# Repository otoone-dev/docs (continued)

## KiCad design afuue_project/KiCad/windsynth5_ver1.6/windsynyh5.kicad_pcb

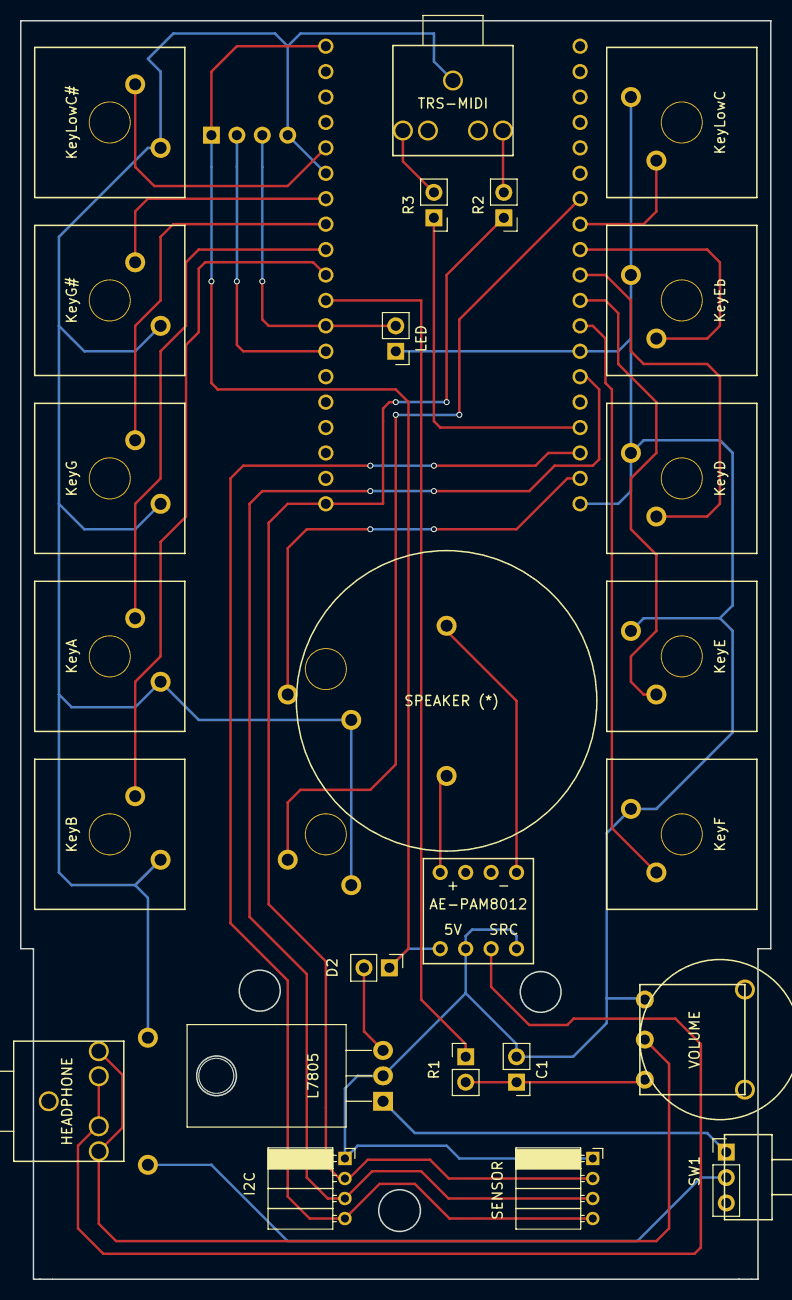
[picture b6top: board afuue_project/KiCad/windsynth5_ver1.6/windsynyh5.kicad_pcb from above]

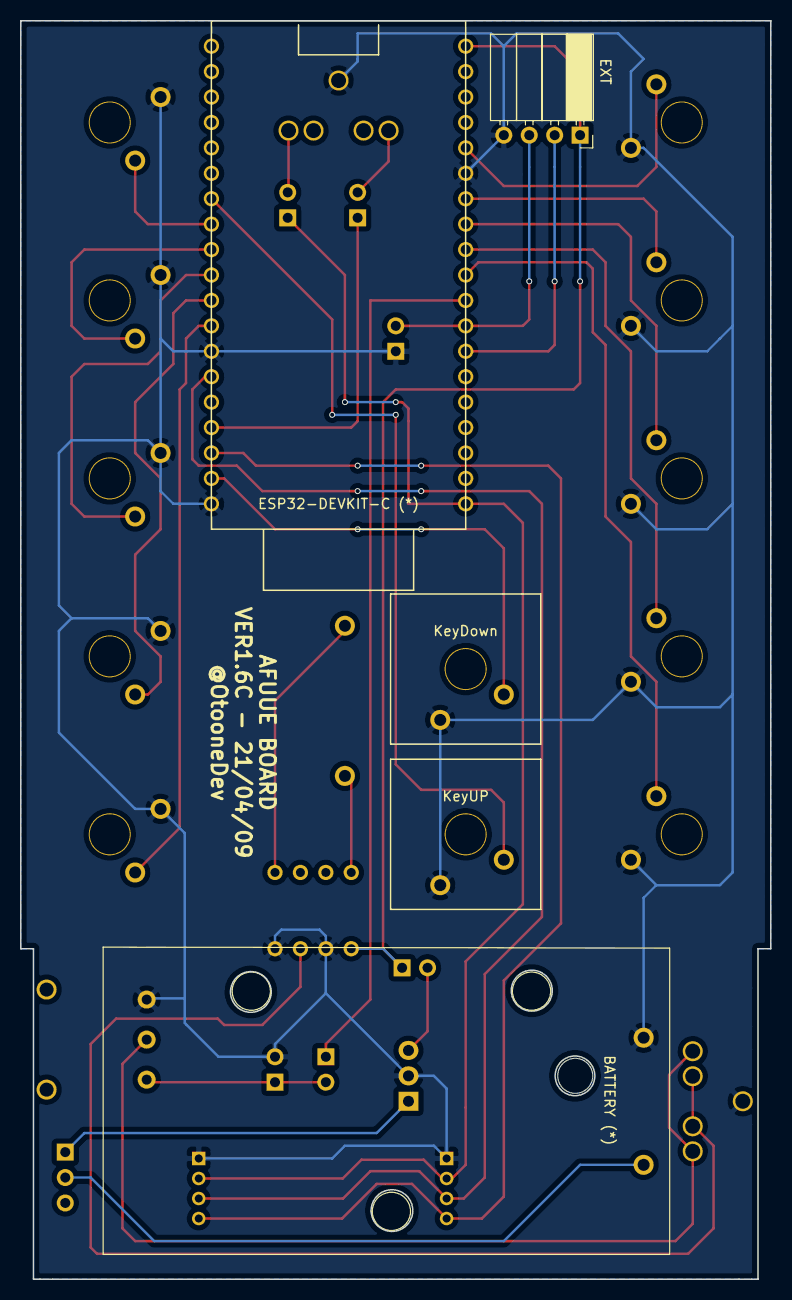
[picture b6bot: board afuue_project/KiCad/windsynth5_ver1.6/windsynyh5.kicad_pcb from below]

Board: 2 copper layers, 74.9 x 125.7 mm, 30 parts (5 on the bottom side), 31 nets.

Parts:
AE-PAM8012: AE-PAM8012
BATTERY (*): POWER; BH-9V-3P24
C1: C; Pin_Header_Straight_1x02_Pitch2.54mm
D2: 1N5822; PinHeader_1x02_P2.54mm_Vertical
ESP32-DEVKIT-C (*): ESP32-DEVKIT-C
EXT: EXT; Socket_Strip_Angled_1x04_Pitch2.54mm
HEADPHONE: HEADPHONE; PJ-307 AudioJack
I2C: I2C; Socket_Strip_Angled_1x04_Pitch2.00mm
KeyA: KeyA; CherryMX-Switch
KeyB: KeyB; CherryMX-Switch
KeyD: KeyD; CherryMX-Switch
KeyDown: KeyDown; CherryMX-Switch
KeyE: KeyE; CherryMX-Switch
KeyEb: KeyEb; CherryMX-Switch
KeyF: KeyF; CherryMX-Switch
KeyG: KeyG; CherryMX-Switch
KeyG#: KeyG#; CherryMX-Switch
KeyLowC: KeyLowC; CherryMX-Switch
KeyLowC#: KeyLowC#; CherryMX-Switch
KeyUP: KeyUp; CherryMX-Switch
L7805: L7805; TO-220-3_Horizontal_TabDown
LED: Led_Small; Pin_Header_Straight_1x02_Pitch2.54mm
R1: 510; Pin_Header_Straight_1x02_Pitch2.54mm
R2, R3: 47; Pin_Header_Straight_1x02_Pitch2.54mm
SENSOR: SENSOR; Socket_Strip_Angled_1x04_Pitch2.00mm
SPEAKER (*): SPEAKER; USGM30
SW1: SW_SPDT; PinHeader_1x03_P2.54mm_Vertical
TRS-MIDI: TRS MIDI; PJ-307 AudioJack
VOLUME: POT; R1001-N16

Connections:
+5V: AE-PAM8012.1, D2.1, ESP32-DEVKIT-C (*).19, EXT.1
+9V: L7805.1, SW1.1
GND: AE-PAM8012.2, AE-PAM8012.4, BATTERY (*).2, C1.2, ESP32-DEVKIT-C (*).14, ESP32-DEVKIT-C (*).32, ESP32-DEVKIT-C (*).38, EXT.4, HEADPHONE.1, I2C.1, KeyA.2, KeyB.2, KeyD.2, KeyDown.2, KeyE.2, KeyEb.2, KeyF.2, KeyG.2, KeyG#.2, KeyLowC.2, KeyLowC#.2, KeyUP.2, L7805.2, LED.1, SENSOR.1, TRS-MIDI.1, VOLUME.1
unnamed: C1.1, R1.2, VOLUME.3
unnamed: ESP32-DEVKIT-C (*).8, EXT.3, LED.2
unnamed: D2.2, L7805.3
unnamed: ESP32-DEVKIT-C (*).11, KeyA.1
unnamed: ESP32-DEVKIT-C (*).10, KeyB.1
unnamed: ESP32-DEVKIT-C (*).29, KeyD.1
unnamed: ESP32-DEVKIT-C (*).37, KeyDown.1
unnamed: ESP32-DEVKIT-C (*).30, KeyE.1
unnamed: ESP32-DEVKIT-C (*).28, KeyEb.1
unnamed: ESP32-DEVKIT-C (*).31, KeyF.1
unnamed: ESP32-DEVKIT-C (*).12, KeyG.1
unnamed: ESP32-DEVKIT-C (*).13, KeyG#.1
unnamed: ESP32-DEVKIT-C (*).27, KeyLowC.1
unnamed: ESP32-DEVKIT-C (*).15, KeyLowC#.1
unnamed: ESP32-DEVKIT-C (*).26, KeyUP.1
unnamed: ESP32-DEVKIT-C (*).1, I2C.2, R2.1, SENSOR.2
unnamed: ESP32-DEVKIT-C (*).33, I2C.3, SENSOR.3
unnamed: ESP32-DEVKIT-C (*).36, I2C.4, SENSOR.4
unnamed: AE-PAM8012.5, SPEAKER (*).1
unnamed: AE-PAM8012.8, SPEAKER (*).2
unnamed: HEADPHONE.2, HEADPHONE.5, VOLUME.2
unnamed: AE-PAM8012.3, HEADPHONE.3, HEADPHONE.4
unnamed: BATTERY (*).1, SW1.2
unnamed: ESP32-DEVKIT-C (*).7, EXT.2
unnamed: R3.2, TRS-MIDI.2
unnamed: R2.2, TRS-MIDI.5
unnamed: ESP32-DEVKIT-C (*).9, R1.1
unnamed: ESP32-DEVKIT-C (*).35, R3.1

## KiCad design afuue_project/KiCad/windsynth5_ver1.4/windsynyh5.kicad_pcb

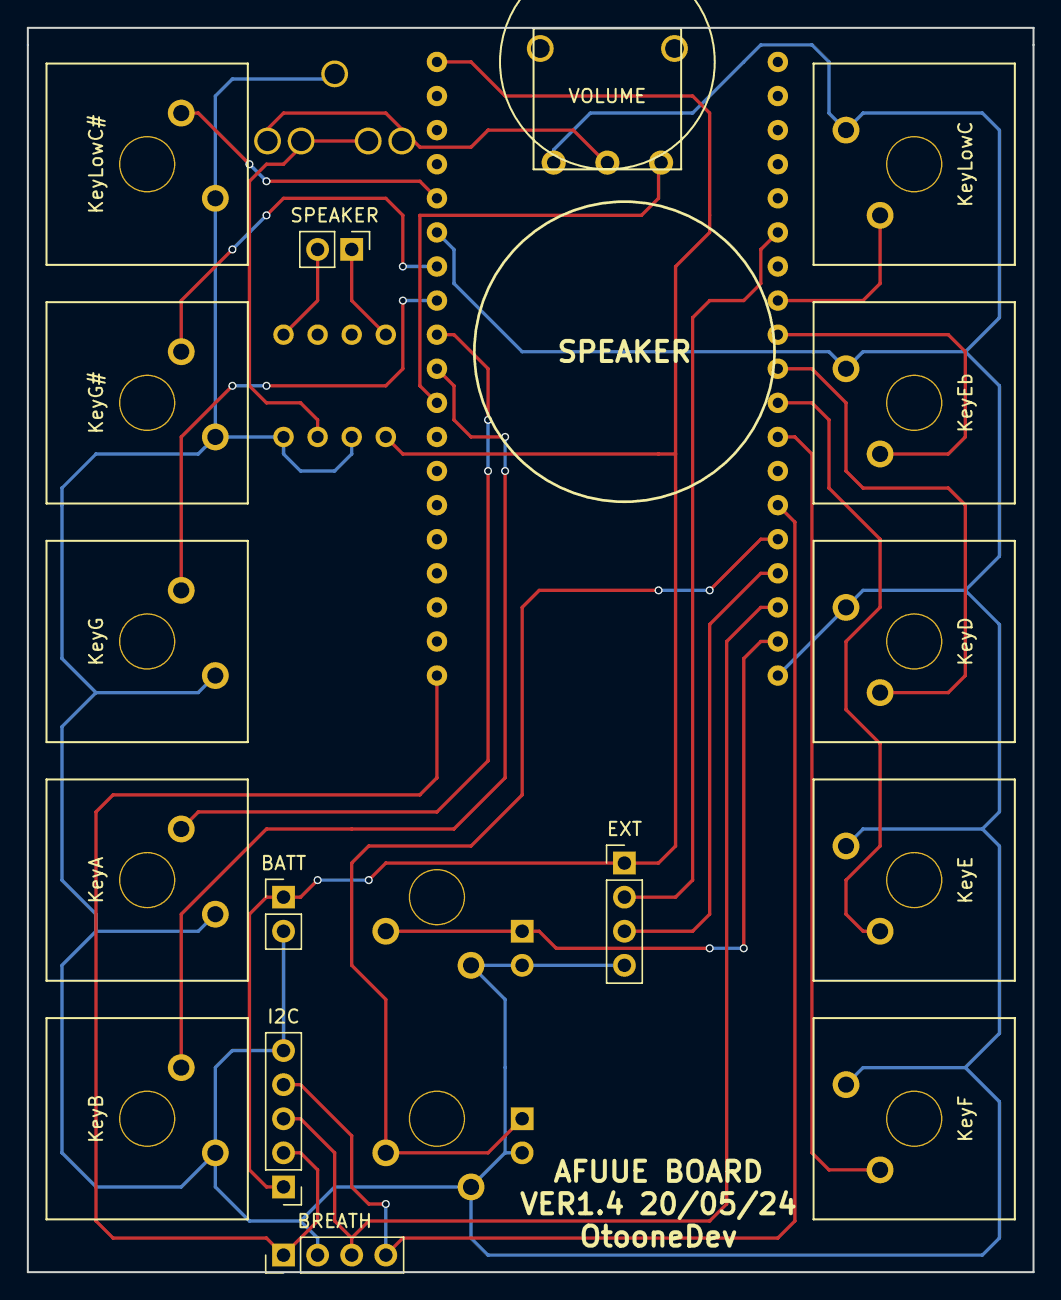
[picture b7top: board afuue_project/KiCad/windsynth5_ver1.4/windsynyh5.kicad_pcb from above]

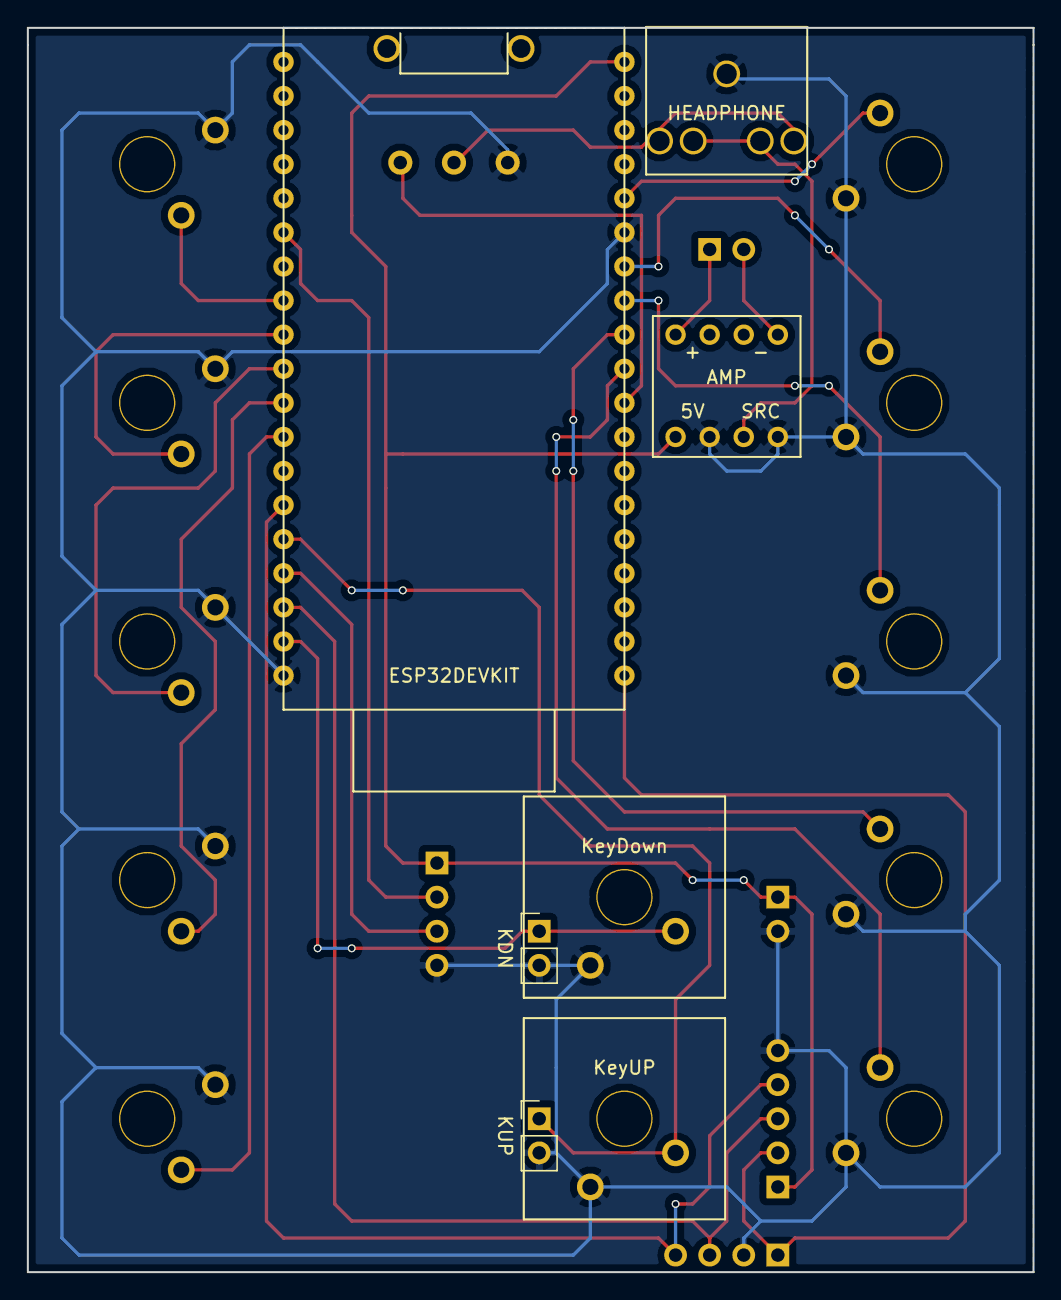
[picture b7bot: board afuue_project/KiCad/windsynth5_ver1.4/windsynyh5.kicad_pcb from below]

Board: 2 copper layers, 74.9 x 92.7 mm, 23 parts (7 on the bottom side), 24 nets.

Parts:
AMP: AE-PAM8012
BATT: EXT-POWER; Pin_Header_Straight_1x02_Pitch2.54mm
BREATH: SENSOR; Pin_Header_Straight_1x04_Pitch2.54mm
ESP32DEVKIT: ESP32-DEVKIT-C
EXT: EXT; Pin_Header_Straight_1x04_Pitch2.54mm
HEADPHONE: HEADPHONE; PJ-307 AudioJack
I2C: I2C; Pin_Header_Straight_1x05_Pitch2.54mm
KDN: KeyDown2; Pin_Header_Straight_1x02_Pitch2.54mm
KUP: KeyUp2; Pin_Header_Straight_1x02_Pitch2.54mm
KeyA: KeyA; CherryMX-Switch
KeyB: KeyB; CherryMX-Switch
KeyD: KeyD; CherryMX-Switch
KeyDown: KeyDown; CherryMX-Switch
KeyE: KeyE; CherryMX-Switch
KeyEb: KeyEb; CherryMX-Switch
KeyF: KeyF; CherryMX-Switch
KeyG: KeyG; CherryMX-Switch
KeyG#: KeyG#; CherryMX-Switch
KeyLowC: KeyLowC; CherryMX-Switch
KeyLowC#: KeyLowC#; CherryMX-Switch
KeyUP: KeyUp; CherryMX-Switch
SPEAKER: SPEAKER; Pin_Header_Straight_1x02_Pitch2.54mm
VOLUME: POT; R1001-N16

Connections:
+5V: AMP.1, BATT.1, ESP32DEVKIT.19, EXT.1, I2C.1
GND: AMP.2, AMP.4, BATT.2, BREATH.2, ESP32DEVKIT.14, ESP32DEVKIT.38, EXT.4, HEADPHONE.1, I2C.5, KDN.2, KUP.2, KeyA.2, KeyB.2, KeyD.2, KeyDown.2, KeyE.2, KeyEb.2, KeyF.2, KeyG.2, KeyG#.2, KeyLowC.2, KeyLowC#.2, KeyUP.2, VOLUME.1
unnamed: ESP32DEVKIT.11, KeyA.1
unnamed: ESP32DEVKIT.10, KeyB.1
unnamed: ESP32DEVKIT.29, KeyD.1
unnamed: ESP32DEVKIT.37, KDN.1, KeyDown.1
unnamed: ESP32DEVKIT.30, KeyE.1
unnamed: ESP32DEVKIT.28, KeyEb.1
unnamed: ESP32DEVKIT.31, KeyF.1
unnamed: ESP32DEVKIT.12, KeyG.1
unnamed: ESP32DEVKIT.13, KeyG#.1
unnamed: ESP32DEVKIT.27, KeyLowC.1
unnamed: ESP32DEVKIT.15, KeyLowC#.1
unnamed: ESP32DEVKIT.34, KUP.1, KeyUP.1
unnamed: BREATH.1, ESP32DEVKIT.1, I2C.2
unnamed: BREATH.3, ESP32DEVKIT.36, I2C.3
unnamed: BREATH.4, ESP32DEVKIT.33, I2C.4
unnamed: AMP.5, SPEAKER.1
unnamed: AMP.8, SPEAKER.2
unnamed: HEADPHONE.2, HEADPHONE.5, VOLUME.2
unnamed: AMP.3, HEADPHONE.3, HEADPHONE.4
unnamed: ESP32DEVKIT.25, EXT.2
unnamed: ESP32DEVKIT.35, EXT.3
unnamed: ESP32DEVKIT.9, VOLUME.3

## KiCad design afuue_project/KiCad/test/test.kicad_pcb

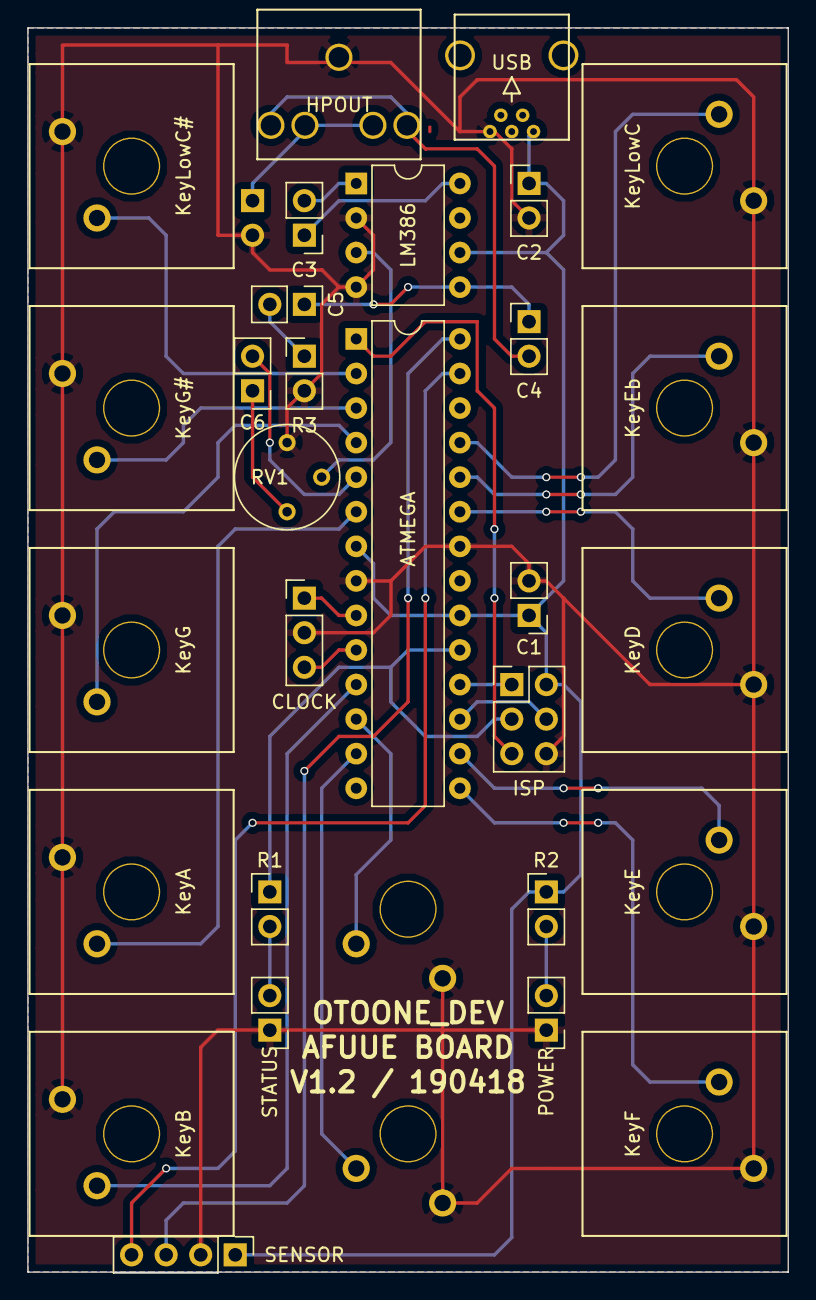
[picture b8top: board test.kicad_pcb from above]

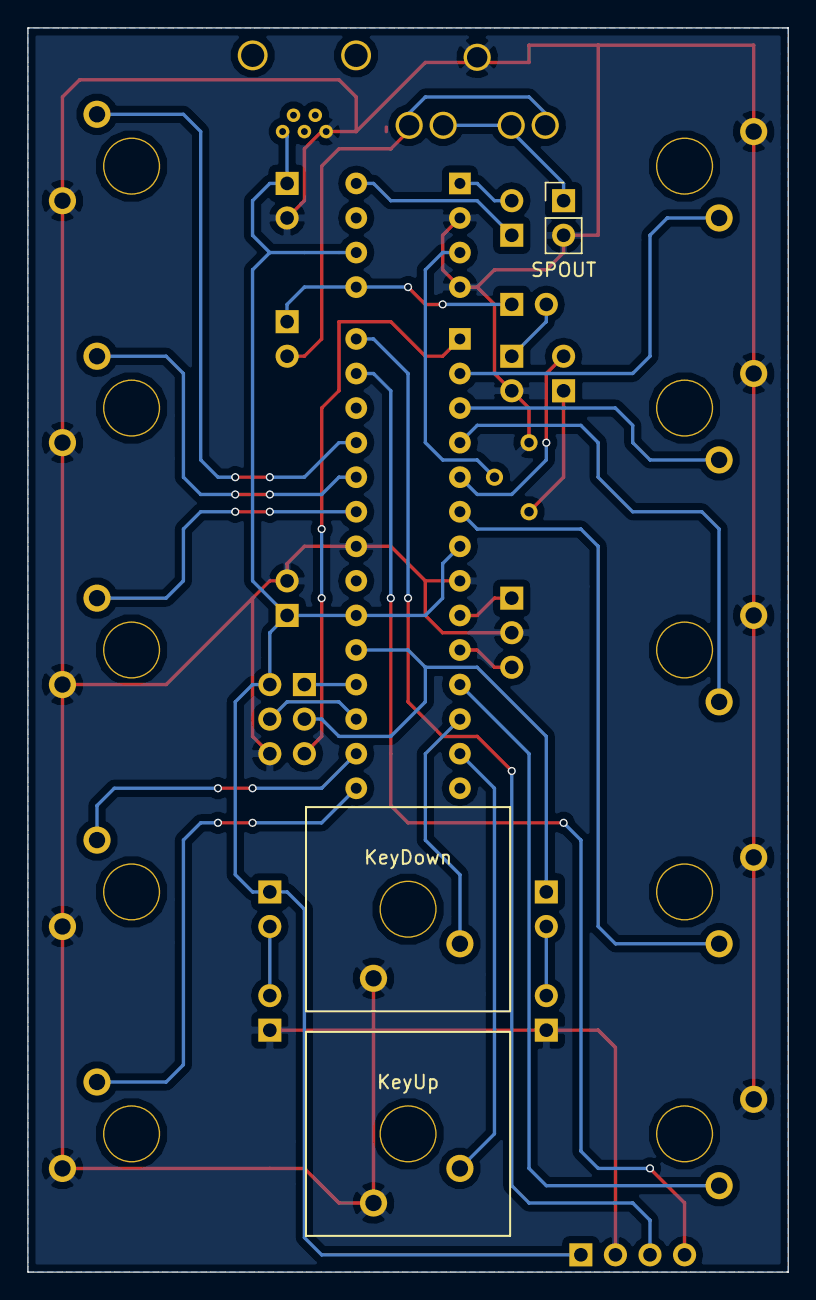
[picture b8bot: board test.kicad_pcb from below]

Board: 2 copper layers, 55.9 x 91.4 mm, 32 parts (3 on the bottom side), 33 nets.

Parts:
ATMEGA: ATMEGA328-P; DIP-28_W7.62mm
C1, C3, C5, C6: C; Pin_Header_Straight_1x02_Pitch2.54mm
C2, C4: CP1; Pin_Header_Straight_1x02_Pitch2.54mm
CLOCK: CLOCK; Pin_Header_Straight_1x03_Pitch2.54mm
HPOUT: HPOUT; PJ-307 AudioJack
ISP: ISP; Pin_Header_Straight_2x03_Pitch2.54mm
KeyA: KeyA; CherryMX-Switch
KeyB: KeyB; CherryMX-Switch
KeyD: KeyD; CherryMX-Switch
KeyDown: KeyOctDown; CherryMX-Switch
KeyE: KeyE; CherryMX-Switch
KeyEb: KeyEb; CherryMX-Switch
KeyF: KeyF; CherryMX-Switch
KeyG: KeyG; CherryMX-Switch
KeyG#: KeyG#; CherryMX-Switch
KeyLowC: KeyLowC; CherryMX-Switch
KeyLowC#: KeyLowC#; CherryMX-Switch
KeyUp: KeyOctUp; CherryMX-Switch
LM386: LM386; DIP-8_W7.62mm
POWER: LED; Pin_Header_Straight_1x02_Pitch2.54mm
R1, R2, R3: R; Pin_Header_Straight_1x02_Pitch2.54mm
RV1: POT; Potentiometer_Trimmer_Bourns_3339P_Horizontal
SENSOR: BMP180; Pin_Header_Straight_1x04_Pitch2.54mm
SPOUT: SPOUT; Pin_Header_Straight_1x02_Pitch2.54mm
STATUS: LED; Pin_Header_Straight_1x02_Pitch2.54mm
USB: miniUSB; miniUSB(USB32BJ)

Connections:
+5V: ATMEGA.7, ATMEGA.20, C1.1, C2.1, ISP.2, LM386.6, R2.1, SENSOR.1, USB.1
GND: ATMEGA.8, ATMEGA.22, C1.2, C2.2, CLOCK.2, HPOUT.1, ISP.6, KeyA.2, KeyB.2, KeyD.2, KeyDown.2, KeyE.2, KeyEb.2, KeyF.2, KeyG.2, KeyG#.2, KeyLowC.2, KeyLowC#.2, KeyUp.2, LM386.2, LM386.4, POWER.1, R3.2, RV1.1, SENSOR.2, SPOUT.2, STATUS.1, USB.5
unnamed: C3.1, LM386.8
unnamed: C3.2, LM386.1
unnamed: C4.1, C5.1, LM386.5
unnamed: C4.2, HPOUT.2, HPOUT.5
unnamed: C5.2, R3.1
unnamed: C6.1, RV1.3
unnamed: ATMEGA.5, C6.2
unnamed: ATMEGA.9, CLOCK.1
unnamed: ATMEGA.10, CLOCK.3
unnamed: HPOUT.3, HPOUT.4, SPOUT.1
unnamed: ATMEGA.1, ISP.5
unnamed: ATMEGA.2, KeyLowC#.1
unnamed: ATMEGA.3, KeyG#.1
unnamed: ATMEGA.4, KeyG.1
unnamed: ATMEGA.6, KeyA.1
unnamed: ATMEGA.11, KeyB.1
unnamed: ATMEGA.12, KeyDown.1
unnamed: ATMEGA.13, KeyUp.1
unnamed: ATMEGA.15, KeyF.1
unnamed: ATMEGA.16, KeyE.1
unnamed: ATMEGA.17, ISP.4
unnamed: ATMEGA.18, ISP.1
unnamed: ATMEGA.19, ISP.3, R1.1
unnamed: ATMEGA.23, KeyD.1
unnamed: ATMEGA.24, KeyEb.1
unnamed: ATMEGA.25, KeyLowC.1
unnamed: ATMEGA.27, SENSOR.4
unnamed: ATMEGA.28, SENSOR.3
unnamed: POWER.2, R2.2
unnamed: R1.2, STATUS.2
unnamed: LM386.3, RV1.2

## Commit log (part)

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2017-02-26 test add
2017-02-27 rename
2017-02-27 Revert "rename"
    This reverts commit 985c1794c650215d0eb9297a111cc48507c178e0.
2017-03-11 pebble
2017-04-19 futako.txt
2017-04-22 .\train_setting.html
2017-04-26 .\train_setting_sample.html
2017-05-08 .\map_setting.html
2017-05-30 .\bio_setting.html
2017-06-13 .\watchface_setting.html
2017-12-25 .\watch_bg.png
2017-12-27 watch_bg.png
2017-12-30 .\watchface_creating.html
2018-01-03 .\pebbledoc.txt
2018-01-07 .\watchface_creating_sample.html
2019-05-07 otooneページ追加
2019-05-09 組み立てマニュアルの準備
2019-05-09 afuue_project 追加
2019-05-09 afuue_project に Model3D を追加
2019-05-09 otoone ページに情報追加
2019-05-09 タグ修正
2019-05-13 AFUUE 組み立て行程に写真追加
2019-05-13 ２音合成
2020-06-01 情報を５号機のものに更新
2020-06-01 画像追加忘れ
2020-06-01 動画を追加
2020-06-01 ブレスセンサーの 3D データと、モニタソフトの zip を配置
2020-06-01 Arduino のソースも追加
2020-06-03 ブレスセンサーのモニターにレンジとテスト範囲の設定と保存ができるように改造
2020-06-04 AFUUE の基板写真を追加
2020-08-01 運指の変更(Bb含めて全般)、MIDI 出力対応
2020-08-01 インストール方法のページを追加
2020-08-01 AFUUE ページに各部名称と運指を追加
2020-08-01 otoone ページから afuue へのリンクを追加
2020-08-01 ファイル名修正
2020-08-01 再度ファイル名修正
2020-08-05 マニュアルなどを追加
2020-08-05 マニュアルに日本語一部追加
2020-08-12 使用ツール説明用
2020-08-18 設定ツールの追加と、ツールとの通信対応など
2020-08-18 exe と obj を削除
2020-08-19 説明更新
2020-08-19 説明追加
2020-09-01 ページの情報を修正
2020-09-05 KiCad データは ver.1.5 に向けて改造中。 AFUUE ソース、ツールともに下記の機能を追加、機能改善 ・ 通信同期 ・ ノイズ、ピッチを音量で可変 ・ メトロノーム ・ 和音
2020-09-05 不要ファイルの削除
2020-09-10 名刺の画像追加
2020-09-10 和音の sus4 を 7th に変更
2020-09-10 HelpWindow 追加
2020-09-14 和音操作方法変更、MIDIコントロール追加、Preferences保存失敗を修正
2020-10-08 AFUUE page の改善、MakerFaireTokyo2020向けのポップ、次期基板への準備など
2020-10-23 現状のものを一旦コミット（KORG NTS-1対応含む）
2020-11-03 基板発注したので
2021-03-27 電池内蔵版v06のソースやデータを追加
2021-03-27 v06 のソフトウェア(zip)を追加
2021-03-28 ページを更新
2021-04-03 v1.6 のマニュアル追加
2021-04-25 v6向け更新
2021-05-07 ページなどを更新
2021-05-11 ３Ⅾデータを２つ追加
2021-12-04 pc-1245(2021/11/23版) SPI, I2C に問題がある
2021-12-04 PC1245 (2021/11/23版) SPI/I2C 回路に問題がある
2021-12-04 2021/10/10 版。 ALLPCB に発注したのは、この中の１枚だけ
2021-12-04 2021/12/03 版 M5StickC 版 9 キー AFUUE 基板
2022-05-10 Core2 向けドラム
2022-05-10 StickC 向け AFUUE
2022-05-10 AfuueEditor をとりあえず追加
2022-05-10 kicad library 追加
2022-05-10 kicad windsynth8 を windsynth8a にリネーム
2022-05-10 kicad windsynth8b を追加
2022-05-10 kicad windsynth7 を追加
2022-09-07 9号機の基板(Kailhロープロファイル&PCF8574T版)を発注したのでコミット
2022-09-07 傾きによる「がなり」などをテスト実装
2022-09-07 9号機の初期ソースをいったんコミット
2022-12-07 AFUUE2(v9)向け販売時ソース
2022-12-07 AFUUE2(v9)基板データ
2022-12-07 AFUUE2(v9)用マニュアル
2022-12-07 AFUUE2(v9)用3Dモデルデータ
2023-05-05 AFUUE_v09 ソースコードzip 追加など
2023-05-05 windsynth10 基板データ追加
2023-05-05 ドキュメント更新
2023-05-22 afuue2R
2023-05-22 ShieldMachine
2023-05-22 AFUUE2R_CAD
2023-07-13 AFUUE2 PWMx2 Version (1.9c)
2023-09-01 2PWM 版の AFUUE2 ソフトウェア
2024-01-08 arduino ソースを３つ追加
2024-01-08 arduino ソース１つ追加
2024-02-29 テスト波形が入っていたので修正
2024-03-02 ホームページを更新
2024-05-06 add pictures of AFUUE2R
2024-06-26 added StampS3
2024-11-21 LPS33対応（アドレス違い＝センサー２個には未対応）
2025-01-01 波形生成テスト
2025-01-01 LowPassフィルタ追加
2025-01-01 drum test
2025-01-02 ローパス計算を波形生成の外に
2025-01-02 ローパスの計算を波形生成の外に。波形シフトを無効に
2025-01-03 クリティカルセクション記述追加、ローパスパラメータ変更
2025-01-05 波形生成をタイマーから分離して float 演算化
2025-01-05 ローパスフィルタテスト実装
2025-01-07 ローパス演算の高速化、三角関数テーブルを大きいものに変更
2025-01-12 高速化とメニューまわり調整
2025-01-16 アタックをプリセット化。M5StickCへのCanvas対応。
2025-01-20 Menu関係、キー操作関係、波形生成関係をソース分離中
2025-01-21 AFUUE2R で操作時に音が鳴らない不具合の修正
2025-01-26 気圧センサー読み取り部分を別ソースに分離
2025-01-29 リファクタリング
2025-02-03 リコーダー追加（音量でのピッチ変更）、リファクタリング
2025-02-04 AFUUE2, AFUUE2R ソースzip
2025-02-04 初期リリース版
2025-02-04 パラメータ微調整したもの
2025-02-04 パラメータ微調整
2025-02-04 マニュアルを更新
2025-02-05 ページ更新
2025-02-06 説明ページ追記
2025-02-06 HasDisplay とかの関数を廃止
2025-02-10 ドラムを追加
2025-02-15 ドラムモード更新
2025-02-27 ドラムの波形を変更
2025-02-27 AFUUE2R でオプション操作が効いてなかったのを修正、番号指定の音色変更に対応
2025-02-27 不具合修正、ドラム追加(AFUUE2のみ)、番号指定音色変更(AFUUE2Rのみ)
2025-02-27 AccDrum追加
2025-03-02 テストコード追加
2025-03-06 ルービックキューブ風の描画を追加
2025-03-21 AFUUE2R gen2 対応中
2025-06-12 テストコードを追加
2025-07-20 v10 lite manual
2025-09-02 AFUUE2R gen2 対応 (LPS33x2)
2025-09-15 LPS33 + MCP23017 の I2C 競合を解決
2025-09-18 処理時間の調整
2025-10-19 動作COREを変更
2025-11-19 音源ボード向けコード追加
2025-11-24 AFUUE2,AFUUE2R,tone_generator のソース追加
2025-12-14 とりあえず MIDI 受けて鳴るように
2025-12-16 音源にとりあえずメニューを追加（うまく動いてない）
2025-12-17 AFUUE_soundtest に AFUUE2 First 追加
2025-12-20 STAMPS3 と ATOMS3 の LED を追加
2025-12-28 AFUUE2R Lite 向け微修正
2025-12-30 PlatformIO環境追加 （AFUUE2R gen2 で I2C 以外のサンプル実装)
2025-12-30 PlatformIO版、I2CによるLPS33制御とATOMS3の画面制御を追加
2026-01-02 ソース分離、MCPWM 採用 MCPWM は LEDC より高速更新が可能。LEDC が 5us ほどかかってたところ MCPWM は 1us。
2026-01-02 負荷表示対応、MCPWM を 16bit に
2026-01-03 PlatformIO版をリングバッファに
2026-01-05 ノイズ対策の試行錯誤中 いろいろやったが、結局 M5AtomS3 だと M5.begin あたりを通るとノイズが発生する模様 M5AtomS3 Lite だとそれほどノイズ出ないかも
2026-01-06 波形生成を分離。波形テーブル音源とディレイを追加。
2026-01-06 フィルタ追加
2026-01-06 キーの反応を鈍化、波形生成調整
2026-01-08 気圧センサー(LPS33)２つの読み込みに対応、ベンド操作に対応
2026-01-08 LPS33初期化修正、M5AtomLite対応修正
2026-01-12 ソース整理
2026-01-14 ハードウェア切り替え対応中
2026-01-15 FastLEDをやめてNeopixelに変更
2026-01-15 サウンドプロセッサを外から注入する形に変更
2026-01-15 音色切り替えに簡易対応
2026-01-19 Menu追加中
2026-01-19 M5StickCでピエゾ
2026-01-23 キーによるメニュー操作に対応（音色切り替えとトランポーズのみ）
2026-01-25 AFUUE2R向けメニューを整備
2026-01-28 MIDI対応準備
2026-01-29 LFOテスト実装、LED不具合修正
2026-02-11 USBMIDIとりあえず動く
2026-02-12 SerialMIDI対応
2026-02-16 ベンド修正、MIDIのNoteOn/Off修正
2026-02-19 ロゴ追加、LFO調整
2026-02-22 MIDI修正、ディスプレイ修正
2026-02-22 MIDI修正、音源実装準備、define整理
2026-02-22 microsオーバーフローをmillisに修正
2026-02-24 v10 gen2 manual
2026-02-25 Preferences対応
2026-02-26 MIDIブレス出力切り替えを追加
2026-02-26 MIDIブレス出力設定にしたがってMIDI出力を切り替え
2026-02-26 ブレス感度修正＆保存
2026-02-27 ノイズ追加、アタック修正、LFO発動時間追加
2026-02-28 ローパスを音程切り替え時にも適用、他パラメータ微調整
2026-04-18 初回コミット
